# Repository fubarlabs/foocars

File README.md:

# What is FOO Cars?

This autonomous vehicle project's goal is to create autonomous racing vehicles in the simplest possible way—a good first car.  The name is a mash-up of Fubar Labs, the mysterious planes called "foo fighters" and "foobar" the ubiquitous getting started variables for programming.  The control system can scale to any vehicles using RC controls.

## How has this project been used?
* CHI@Edge 2022 Summer Internship
 * Virtual exercises to access the Cameras, Serial Devices, GPIO Devices, and Machine Learning Environments
* CHI@Edge 2021 Summer Internship
  * Virtualize the deployment of vehicle and code on the edge of super computer envrionment.

### FUBAR Labs Autonomous Racing Vehicles

Autonmous Vehicle Project at Fubar Labs for the Autonomous Powerwheels Racing compeition.
* Bergen Technical Highschool Workshop Spring 2023
* Bergen Technical Highschool Workshop Spring 2021
* Autonomous Powerwheels Racing Pittsburg Makerfiare 2017
 * We totally did laps. We were on the track on time and ready to go!
* Autonmous Powerwheels Racing Makerfaire NYC 2017
* Autonmous Vehicle Competition via Sparkfun at Denver Makerfaire 2017

## Quickstart

### Car Code

## Prepare your PI

Obtain the car code by cloning the project
```
git clone https://github.com/fubarlabs/foocars
```

For the Tensorflow 1.15 version fetch the wheel file to the local system:
```
cd ~/foocars
sh get_tensorflow.sh
```

Install system packages
```
sudo apt-get  install build-essential cmake pkg-config libjpeg-dev libtiff5-dev libjasper-dev libpng-dev libavcodec-dev libavformat-dev libswscale-dev libv4l-dev libxvidcore-dev libx264-dev libfontconfig1-dev libcairo2-dev libgdk-pixbuf2.0-dev libpango1.0-dev libgtk2.0-dev libgtk-3-dev libatlas-base-dev gfortran libhdf5-dev libhdf5-serial-dev libhdf5-103 libqtgui4 libqtwebkit4 libqt4-test python3-pyqt5

```

Install poetry
```
sudo pip3 install poetry
```

Install platformio
```
sudo pip3 install platformio
```

Use poetry to create the generate the car
```
cd ~/foocars/cargenerator
poetry install
poety run generatecar --name yourhostname --output_dir /home/pi/foocars/cars/
```

Use poetry to create the car code and service
```
cd ~/foocars/cars/carservices
poetry install
```

Test the PI Hat
```
poetry run test_pihat
```

Test the Car Runner
```
poetry run car_runner
```

Verify the leds and switches are working.

## Pepare the RC Car and Arduino

### Note for Arduino
Code is installed from the Raspberry PI using PLatform IO
```
sudo pip3 install platformio

```

### Teensy 3.2 Code

```
cd ./cars/templatecar/arduino/teensy-FullAutoDrive-port
```

### Arduino Code

```
pio run -t upload
```

### Finish the PI set up
Set up the raspberry pi services
```
cd /etc/systemd/system/
sudo ln -s ~/foocars/cars/carservices/carservices/car.service 
sudo systemctl start car
tail -f /var/log/syslog
```
Verify the car service is running the car runner

## Training code

Find a system with a good gpu. It was slow but worked on a Raspberry PI 4.
```
cd ~/foocars/training

poetry install
poetry shell
```
The training command:
```
Using TensorFlow backend.
usage: train.py [-h] [--weight_filename WEIGHT_FILENAME]
                [--init_weights INIT_WEIGHTS] [--delay DELAY]
                [--epochs EPOCHS] [--save_frequency SAVE_FREQUENCY]
                directories [directories ...]
```
Run the training:
```
python train.py --epochs 100 --save_frequency 2 ../cars/youcar/data/collected
```

### Alternately use this example Google Colab Notebook
* FooCars Training: https://colab.research.google.com/drive/1LxZyNQvWT2VasnOrNkU9dTcpo4B9I0aD?usp=sharing

### 2023 Training with Docker

https://colab.research.google.com/drive/1oT3M4QVUoNYkFh4pzktVNBfT0zULwSpM?usp=sharing

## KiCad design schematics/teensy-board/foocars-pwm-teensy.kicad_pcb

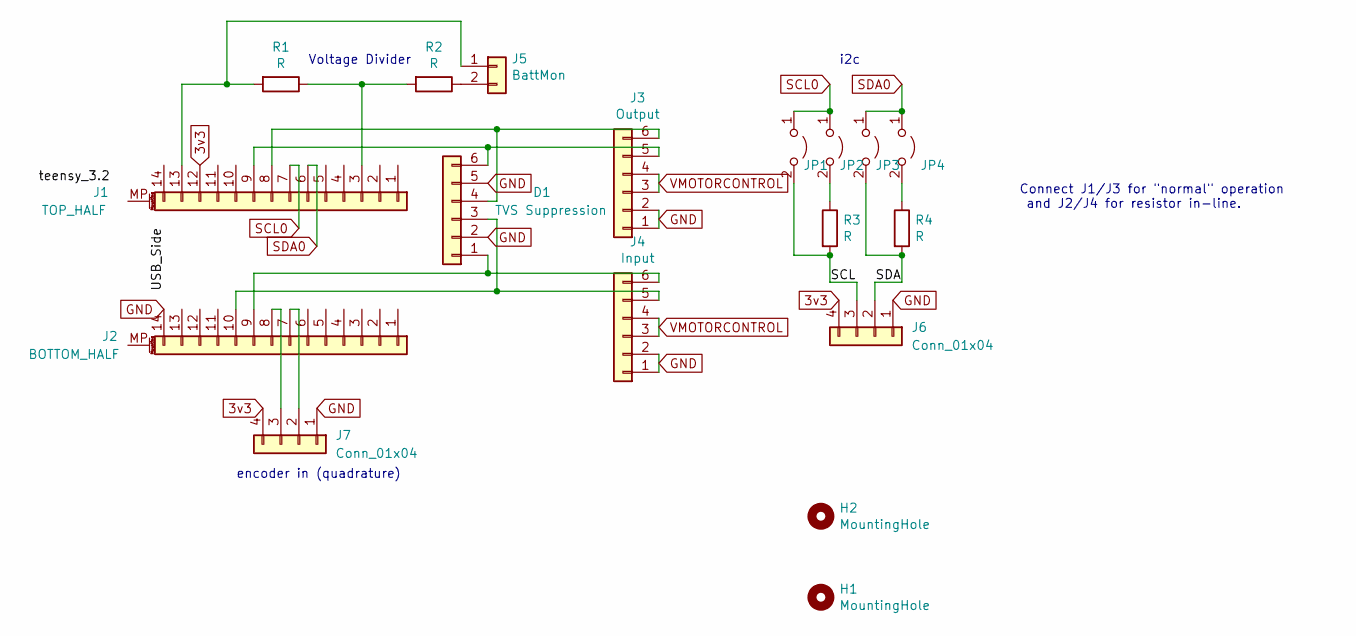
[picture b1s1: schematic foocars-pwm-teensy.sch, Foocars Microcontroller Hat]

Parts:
D1: TVS Suppression; SOT-23-6_Handsoldering
H1, H2: MountingHole; MountingHole_2.5mm_Pad
J1: TOP_HALF; PinSocket_1x14_P2.54mm_Vertical
J2: BOTTOM_HALF; PinSocket_1x14_P2.54mm_Vertical
J3: Output; PinHeader_2x03_P2.54mm_Horizontal
J4: Input; PinHeader_2x03_P2.54mm_Horizontal
J5: BattMon; PinHeader_1x02_P2.54mm_Vertical
J6, J7: Conn_01x04; PinHeader_1x04_P2.54mm_Horizontal
JP1, JP2, JP3, JP4: Jumper_2_Open; SolderJumper-2_P1.3mm_Open_TrianglePad1.0x1.5mm
R1, R2, R3, R4: R; R_Axial_DIN0204_L3.6mm_D1.6mm_P5.08mm_Horizontal

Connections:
3v3: J1.12, J6.4, J7.4
/SCL: J6.3, JP1.2 (B), R3.2
/SDA: J6.2, JP3.2 (B), R4.2
GND: D1.2, D1.5, J2.14, J3.1, J3.2, J4.1, J4.2, J6.1, J7.1
unnamed: D1.1, J2.9, J4.6
unnamed: D1.3, J2.10, J4.5
unnamed: D1.4, J1.8, J3.6
unnamed: D1.6, J1.9, J3.5
unnamed: J1.3, R1.1, R2.2
unnamed: J1.13, J5.1, R1.2
unnamed: J2.7, J7.2
unnamed: J2.8, J7.3
unnamed: J5.2, R2.1
unnamed: JP2.2 (B), R3.1
unnamed: JP4.2 (B), R4.1
SCL0: J1.7, JP1.1 (A), JP2.1 (A)
SDA0: J1.6, JP3.1 (A), JP4.1 (A)
VMOTORCONTROL: J3.3, J3.4, J4.3, J4.4

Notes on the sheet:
Voltage Divider
i2c
Connect J1/J3 for "normal" operation and J2/J4 for resistor in-line.
encoder in (quadrature)

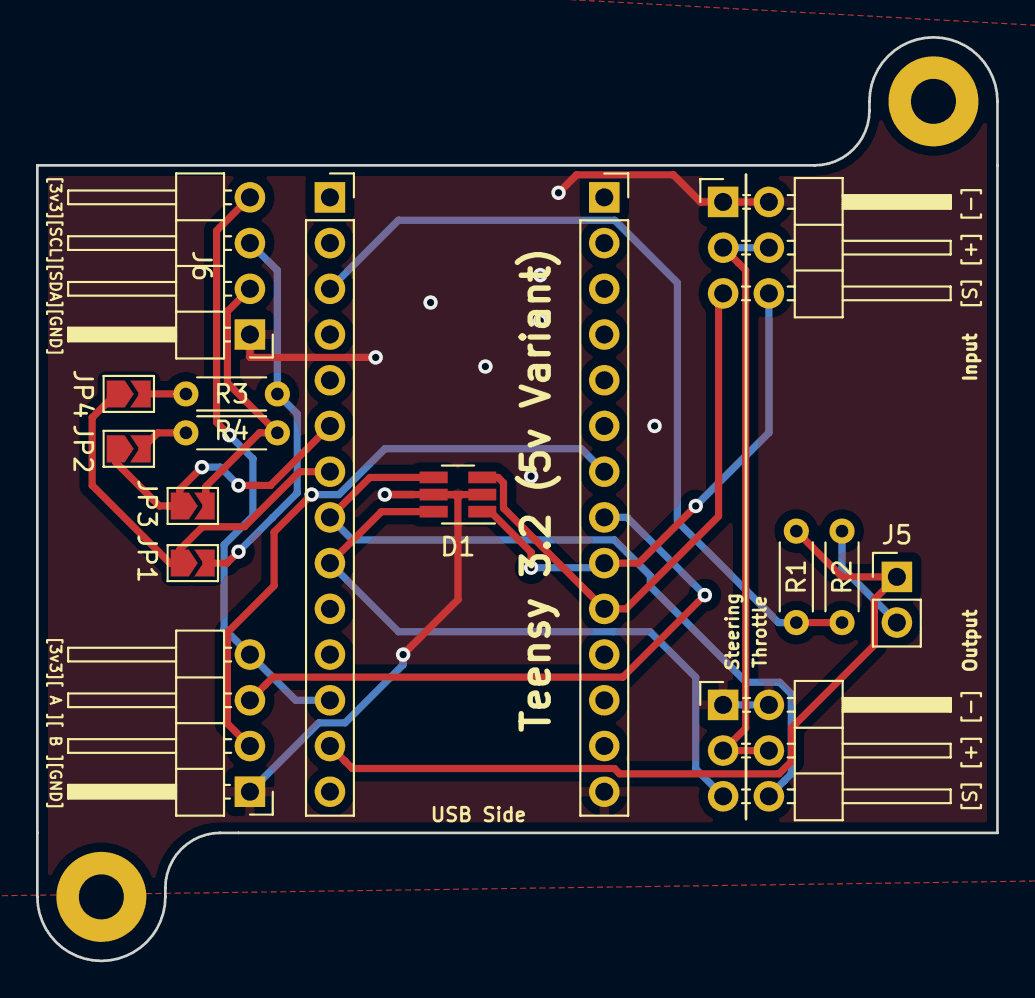
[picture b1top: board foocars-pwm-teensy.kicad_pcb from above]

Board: 2 copper layers, 53.3 x 51.3 mm, 18 parts (0 on the bottom side), 18 nets.

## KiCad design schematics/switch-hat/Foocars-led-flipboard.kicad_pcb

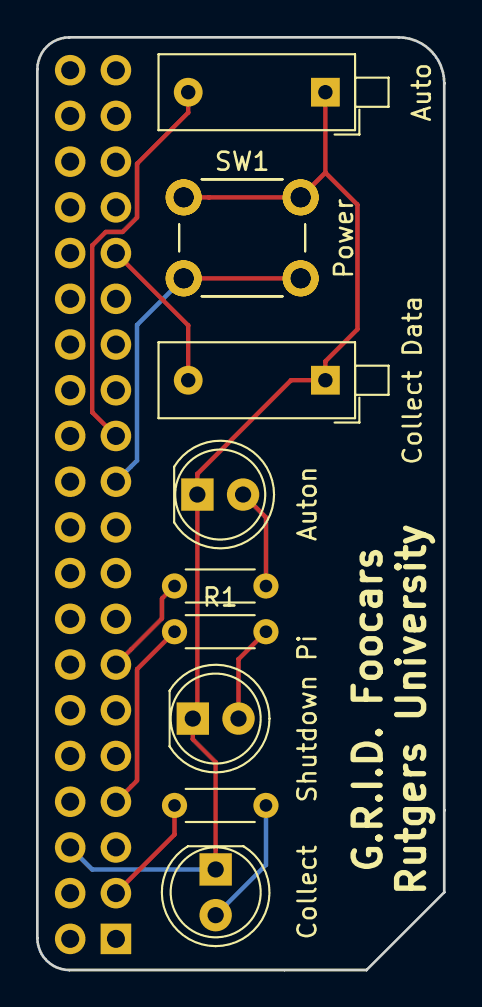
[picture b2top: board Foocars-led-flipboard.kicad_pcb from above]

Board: 2 copper layers, 22.6 x 51.8 mm, 11 parts (1 on the bottom side), 10 nets.

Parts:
Auto: SW_DIP_x01; SW_DIP_SPSTx01_Piano_10.8x4.1mm_W7.62mm_P2.54mm
Auton: LED; LED_D5.0mm
Collect: LED; LED_D5.0mm
Collect Data: SW_DIP_x01; SW_DIP_SPSTx01_Piano_10.8x4.1mm_W7.62mm_P2.54mm
J1: Conn_02x20_Odd_Even; PinSocket_2x20_P2.54mm_Vertical
Power: SW_Push; SW_PUSH_6mm
R1, R2, R3: R; R_Axial_DIN0204_L3.6mm_D1.6mm_P5.08mm_Horizontal
SW1: SW_Push; SW_PUSH_6mm
Shutdown Pi: LED; LED_D5.0mm

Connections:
unnamed: Auto.1, Auton.1, Collect.1, Collect Data.1, J1.6, Power.1, SW1.1, Shutdown Pi.1
unnamed: R1.2, Shutdown Pi.2
unnamed: Collect.2, R2.2
unnamed: Auton.2, R3.2
unnamed: J1.3, R2.1
unnamed: J1.7, R1.1
unnamed: J1.13, R3.1
unnamed: J1.21, Power.2, SW1.2
unnamed: Auto.2, J1.23
unnamed: Collect Data.2, J1.31

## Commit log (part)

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2019-04-16 Update 01_Raspberry_PI_setup.md
    arranged pictures
2019-04-16 Create empty.md
    empty file
2019-04-16 Add files via upload
    uploaded pics for the doc
2019-04-16 Add files via upload
    first version
2019-04-20 Update How To Use Markdown In GitHub.md
    Added pictures
2019-04-20 Add files via upload
    Added pics for tutorial
2019-04-20 Add files via upload
    Initial commit
2019-04-20 Update How To Use GIT on a Raspberry PI.md
    Uploaded pictures
2019-04-20 Create empty.md
    New Folder with empty file
2019-04-20 Add files via upload
    upload pictures
2019-04-20 Update How to use Github to Collaborate With Others.md
    added pictures
2019-04-22 trial
2019-04-24 Update Python Virtual Environments.md
    fixed file
2019-04-24 Update Python Virtual Environments.md
    final tunning
2019-05-01 My own playground copy
2019-05-07 Added fubarino mini input capture code
2019-05-07 added the driving force code
2019-05-12 Converts file into image
2019-05-12 Runs file train.py
2019-05-14 Created using Colaboratory
2019-05-15 Update Foocars_Images_and_Video_from_Data.ipynb
    initial commit
2019-05-15 Delete Copy_of_Foocars_Images_and_Video_from_Data.ipynb
    duplicated
2019-06-12 Added Switch-Palace hat schematic.
2019-07-09 Commit for real.
2019-08-06 Basic tutorial on Google Colab and Python
2019-08-06 Added a basic intro to Google Colab and python
    Worked example explaining Colab and python language
2019-08-07 First draft of Docker file tutorial
2019-08-07 added pics for tutorial
2019-08-07 first draft of Docker tutorial
2019-09-08 Build loss chart at history-agnostic training
2019-09-08 Fix data storage for template car
2019-09-13 added the car generator command line
2019-09-18 Added a train Pipfile for #36
2019-09-18 Update curator Pipfile.
2019-09-27 Added first version
2019-09-30 Added DIA files
    These are the files made for the car's schema
2019-10-02 NO longer used. So removed.
2019-10-02 Add Teensy PWM board current version.
2019-11-01 Updated templatecar to be servicable and make car dir the working one.
2019-11-08 Begun minor cleanup.
2019-11-30 Added presentation from RoboCars workshop
2019-12-12 Uploaded presentation of PID and IMUs
2020-02-19 Updated curator to not need a very old version of scipy.
2020-02-19 Remove SciPy (was single use?)
2020-03-13 Add Pyproject file for Poetry.
2020-03-13 Remove another unused scipy.misc class, copied from other file? Seems to run fine on my system.
2020-03-13 Add Toml for Curator and lock versions that matter
2020-07-14 Uploaded pics for the PyCharm tutorial
    Pics that will be linked to the PyCharm tutorial
2020-07-15 Update Pycharm-tutorial.md
    updated with pics
2020-07-15 Update README.md
    Removed old quick start
2020-07-22 add poetry configuration to generatecar
2020-07-22 Added the default directories for a complete car. Code will need to be placed in here for a car.
2020-07-22 added code to finish car template generation. TODO: Clen up
2020-07-23 more cleanup
2020-07-23 removed bad directory. Added the correct version of the teensy code>
2020-07-23 added the renamed generatecar.py file
2020-08-01 Added the car services project
2020-08-01 Added a cleanup function
2020-08-01 Car Generator initial project
2020-08-02 Got poetry running scripts
2020-08-02 poetry run car_runner is now functional
2020-08-02 Updated car generator
2020-08-02 added name value to output dir
2020-08-02 added the poetry run carservice
2020-08-02 added the car to the out put directory
2020-08-02 added support for import_resources
2020-08-02 removed Pipfile: pipenv no longer supported
2020-08-05 update ricarto data folders
2020-08-05 added default weights to default car
2020-08-05 Added the missing libatlas-base-dev system file.
2020-08-08 Added wheel file for scipy. Fixing install problem on rpi3
2020-08-16 Fix for tf.session and Keras missing localhost
2020-08-17 Google Colan is running python 3.6.9
2020-08-19 Working on fix for directory defaults using toml
2020-08-20 added toml save defaults to config.toml
2020-08-20 Updated PWM hat to have new inputs.
2020-08-27 Added new layout, new pins, added TVS diode.
2020-08-27 Swap ground pins, review with Rick.
2021-01-08 Fixed the swapped STR and THR pins. #62
2021-01-08 #62 swapped the input and output. Confirmed working.
2021-02-22 Added power on LED to the Teensy.
2021-03-02 Online access to the wheel file moved.
    This script fetches it.
2021-03-02 Rename get_tensorflow,sh to get_tensorflow.sh
2021-03-03 Removed the poetry lock to allow for updates
2021-03-03 updated version h5py to < 3.0.0
2021-03-05 defines adjusted to match pihat
2021-04-12 updates to car runner for tensorflow
2021-04-12 Issue #67 fixed by swapping inputs, and output paris.
2021-04-14 Update pyproject.toml
    Added Piwheels to first search for the Raspberry PI wheel before compiling code.
2021-04-14 We have two copies of the same drive system
2021-04-14 updated to piwheels
2021-04-14 Update README.md
    Moved the Arduino code configuration to after the project is cloned.
2021-04-14 system files needed
2021-04-15 Added code to support button throttle change
2021-04-15 Added globals to support the changed variables throughout code
2021-04-30 added test versin of requirements.txt via poetry export
2021-05-03 Added example training notebook.
2021-05-03 Remove pillow version to resolve security issue
2021-07-15 Update Dockerfile-car
2021-08-01 Added Dockerfile update
2021-08-01 updated to multistage docker
2021-08-01 Added the new tensorflow 2.x support and fixed the Dockerfile-car installation.
2021-08-01 Fixed entry point, hash references
2021-08-06 added read the docs for picamera
2021-08-06 use prebuilt tf2.4-py39
2021-08-10 minimal dockerfile
2021-08-10 Added back h5py
2021-08-10 updated to add numpy
2021-08-11 added interactive to docker set up
2021-08-11 added libdhf5-dev for h5py
2021-08-11 Added libhdf5-dev to docker build
2021-08-11 added the test_gpio for switches
2021-08-11 added test directory to build
2021-08-11 attempting to get test directory deployed to final image
2021-08-11 fixed syntax error for gpio test
2021-08-11 fixing syntact error for test_gpio
2021-08-11 adding GPIO.BCM mode
2021-08-11 fixing a typo in switch name
2021-08-11 trying rising vs falling
2021-08-11 added event test
2021-08-11 add the polling test one button code
2021-08-11 fixed time and added push to docker build
2021-08-11 added test for edge detection
2021-08-12 update pihattet syntax error and docker_build update.
2021-08-12 Update docker entrypoint to auto run car
2021-08-12 added volume to dockerfile
2021-08-12 docker cp container info added
2021-08-12 updating to add throttle prediction
2021-08-13 most recent dockerfile
2021-08-13 Windows cant' figure out what case this is. So I deleted the file.
2021-08-13 added camera information to defines.py
2021-08-13 changed names and back to tuples
2021-08-13 added tuples into variable
2021-08-13 fix adding tuples
2021-08-13 fixed tuple issue
2021-08-13 fixed tuple issue by adding two list together
2021-08-13 Issue #84 ottologger to carlogger resolved
2021-08-14 added print statement to say what mode the car is in
2021-08-14 issue #141 first pass at implementing MODEs
2021-08-14 defines.py was out of sync from main
2021-08-14 fixed mode typo
2021-08-14 added camera start to main when in auto mode
2021-08-14 using the callback to do all the work.
2021-08-15 issue #114 made auto_mode global.
2021-08-15 The work of autonomous mode t/f in function
2021-08-15 Code clean up and removed auto_mode from callback
2021-08-15 move globals from callback to autonomous function
2021-08-15 added argparse features
2021-08-15 moved model import after the argparse
2021-08-17 minor mod
2021-08-18 fixes and clear error messages
2021-08-18 added a serial debug
2021-08-18 added a write_log function
2021-08-18 added autodatacollector
2021-08-18 added platformio to docker
2021-08-19 added some debuggng
2021-08-19 more debugging code
2021-08-20 added timout to serial connection
2021-08-20 remove the problem ttyAMA0
2021-08-20 auto_collector needs to save the trained image size
2021-08-20 reversed camera vs auto collect image sizes
2021-08-20 issue #122 max min throttle added defined in defines.py
2021-08-20 removed AUTOMODE message
2021-08-20 commented out everything that breaks, run in auto
2021-08-20 starting cleanup
2021-08-20 working on main
2021-08-20 comment out serail fixe Ex case
2021-08-20 ignore autonomous comman off from RC
2021-08-21 Issue #120 added argparse options for throttle
2021-08-21 Issue #120 free spec the integer
2021-08-21 Issue #120 non specific throttle -1
2021-08-21 Issue #120 added resolution options
2021-08-21 issue #120 removed the image crop to get rid of error
2021-08-21 issue #120 ML models nrows and ncols need to match auto_image_frame
2021-08-21 issue #130 convert models to objects
2021-08-21 issue #131 fixing crop to fix the training size
2021-08-21 issue #131 typo
2021-08-21 issue #131 verifying crop settings
2021-08-21 issue #131 pren problem
2021-08-21 issue #120 if THR_MODE auto then include throttle model
2021-08-21 added thr_val support
2021-08-21 throttle reference issue
2021-08-22 added debug autonomous command
2021-08-22 removed while true from main
2021-08-22 added atexit
2021-08-22 added g_stop_event
2021-08-22 added thread daemon True
2021-08-22 remove extra THR_MAX
2021-08-22 training updates
2021-08-22 adjusted the value logged
2021-08-22 minor fixes
2021-08-22 add github actions
2021-10-29 login to repo and push container
2021-10-29 Test for workflow action to deploy
2021-10-29 changed secrets to docker
2021-10-29 The docker environment is not a keyword need secrets
2021-11-01 Passing secrets as an env variable.
2021-11-01 Added a name: rianders/car
2021-11-01 removed the name: from the with statement
2021-11-02 Added a no terminal version of test_pihat
2021-11-02 Added noterminal test to the poetry run file.
2021-11-02 Removed the sleep function because blocking
2021-11-04 Only build on push which is merge
2021-11-04 Updated insecure dependencies as indicated by dependabot
2021-12-17 Initial changes to support 32 bit Raspberry Pi
2021-12-17 Fix for file reference
2021-12-17 fiing platform references
2021-12-17 Changed poetry installation procedure
2021-12-17 source poetry path
2022-06-16 Moved carsservices to top level directory
2022-06-16 Adjusted documentation and Dockerfile for carservices move
2022-06-16 Update dockerfile
2023-04-16 open new directory bug fix
2023-04-17 remove crash when canceling open
2023-04-17 fixed default directory for open
2023-04-17 fixed the speed multiplier
    replace 12 with 10
2023-04-17 Added confirmaton mesage for save
    For issue #86 notification that files are saved and where
2023-04-17 Added the command data to the display
    Issue #87 added the command data to the display
2023-04-18 Fixed some edge cases and todos about jumping frames
    Fixed some edge cases and todos about jumping frames
2023-04-25 Added the streamlit code. Working on the training data portion after upload
2023-04-25 tensorboard updates
2023-04-25 Moved to version 2 of docker login action
2023-04-25 Update build.yml
    Moved nodejs version to 16
2023-04-25 Added specify know directories with training data
2023-04-29 Added car32 to the build
2023-04-29 Added the output fixes
2023-04-29 Fixing poetry install for car32.dockerfile
2023-04-29 Turn car_runner on right away
2023-04-29 upgrade pip3
2023-04-30 build patched userland for 64bit picamera
2023-04-30 Update build.yml
    Issue #181 removing the automatic build until the issue is resolved.
2023-05-01 ensure glibc version matches between userland and carrunner
2023-05-19 fixed tag bracket order
2023-05-19 added the image dimensions display
2023-05-19 dependency modficiations
2023-05-19 Added the overlay. It's in the wrong place but it's added
2023-05-19 added a zoom feature to the data curator
2023-05-19 First working version with crop area set
